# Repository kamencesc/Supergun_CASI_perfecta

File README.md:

# Supergun_CASI_perfecta
Diseño de un supergun con ciertas caracteristicas, proyecto en los foros de EOL.

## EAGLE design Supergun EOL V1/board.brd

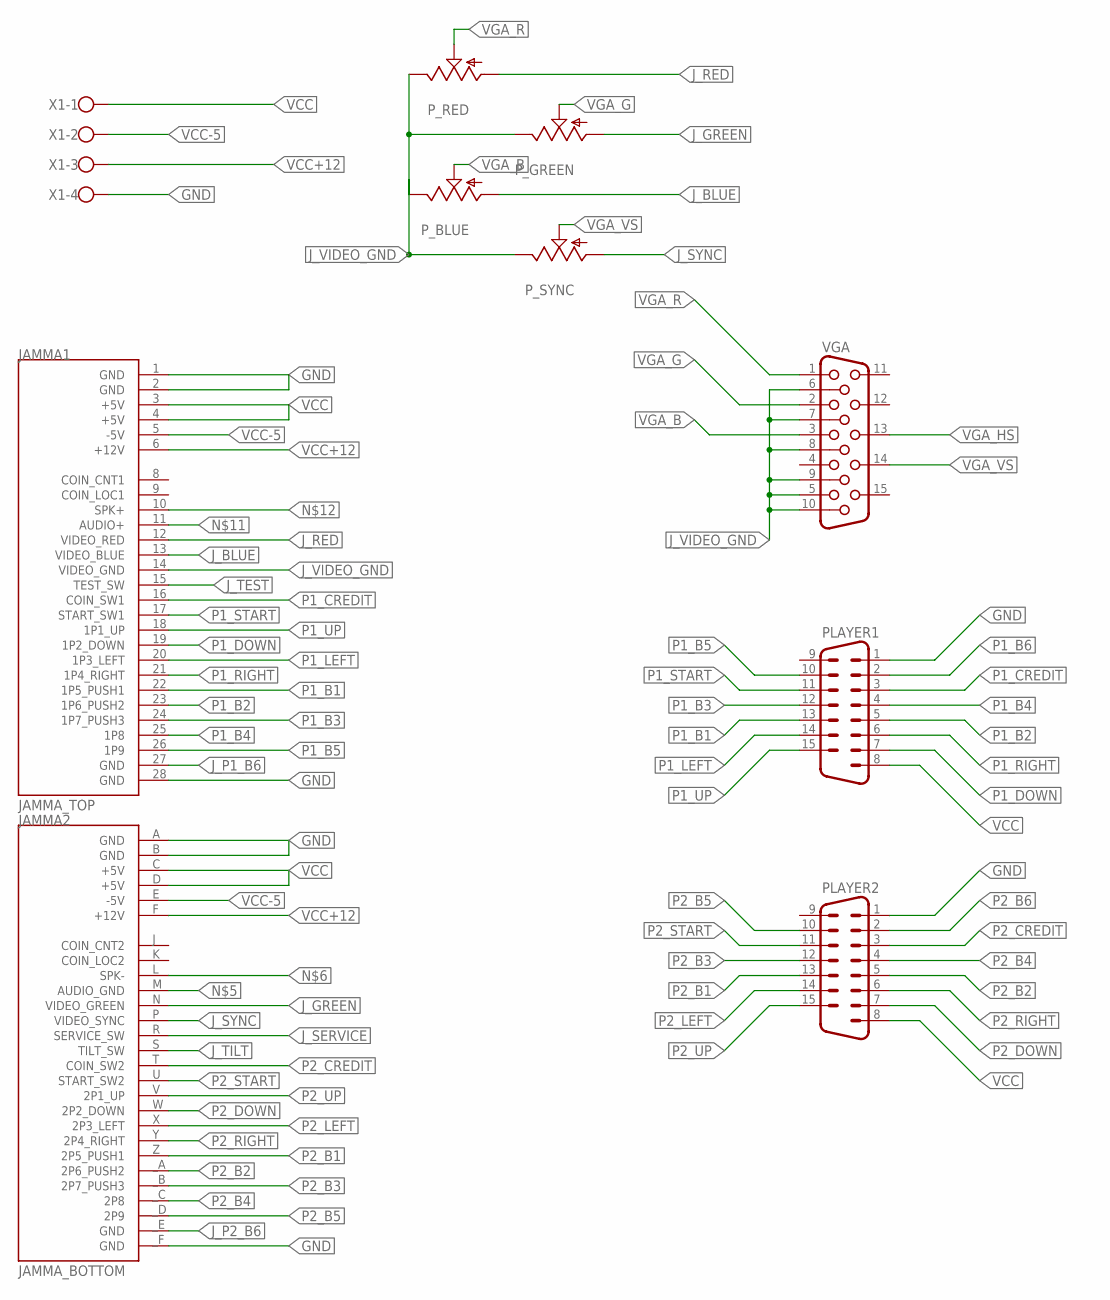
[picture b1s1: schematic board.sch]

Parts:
JAMMA1: JAMMA_TOP
JAMMA2: JAMMA_BOTTOM
PLAYER1, PLAYER2: M15VB
P_BLUE: TRIM_US-B25P; B25P
P_GREEN: TRIM_US-B25P; B25P
P_RED: TRIM_US-B25P; B25P
P_SYNC: TRIM_US-B25P; B25P
VGA: HF15H; HDF15H
X1: W237-4

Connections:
GND: JAMMA1.1 (GND), JAMMA1.2 (GND), JAMMA1.28 (GND), JAMMA2.A (GND), JAMMA2.B (GND), JAMMA2._F (GND), PLAYER1.1, PLAYER2.1, X1.4
J_BLUE: JAMMA1.13 (VIDEO_BLUE), P_BLUE.A
J_GREEN: JAMMA2.N (VIDEO_GREEN), P_GREEN.A
J_P1_B6: JAMMA1.27 (GND)
J_P2_B6: JAMMA2._E (GND)
J_RED: JAMMA1.12 (VIDEO_RED), P_RED.A
J_SERVICE: JAMMA2.R (SERVICE_SW)
J_SYNC: JAMMA2.P (VIDEO_SYNC), P_SYNC.A
J_TEST: JAMMA1.15 (TEST_SW)
J_TILT: JAMMA2.S (TILT_SW)
J_VIDEO_GND: JAMMA1.14 (VIDEO_GND), P_BLUE.E, P_GREEN.E, P_RED.E, P_SYNC.E, VGA.5, VGA.6, VGA.7, VGA.8, VGA.9, VGA.10
P1_B1: JAMMA1.22 (1P5_PUSH1), PLAYER1.13
P1_B2: JAMMA1.23 (1P6_PUSH2), PLAYER1.5
P1_B3: JAMMA1.24 (1P7_PUSH3), PLAYER1.12
P1_B4: JAMMA1.25 (1P8), PLAYER1.4
P1_B5: JAMMA1.26 (1P9), PLAYER1.10
P1_B6: PLAYER1.2
P1_CREDIT: JAMMA1.16 (COIN_SW1), PLAYER1.3
P1_DOWN: JAMMA1.19 (1P2_DOWN), PLAYER1.7
P1_LEFT: JAMMA1.20 (1P3_LEFT), PLAYER1.14
P1_RIGHT: JAMMA1.21 (1P4_RIGHT), PLAYER1.6
P1_START: JAMMA1.17 (START_SW1), PLAYER1.11
P1_UP: JAMMA1.18 (1P1_UP), PLAYER1.15
P2_B1: JAMMA2.Z (2P5_PUSH1), PLAYER2.13
P2_B2: JAMMA2._A (2P6_PUSH2), PLAYER2.5
P2_B3: JAMMA2._B (2P7_PUSH3), PLAYER2.12
P2_B4: JAMMA2._C (2P8), PLAYER2.4
P2_B5: JAMMA2._D (2P9), PLAYER2.10
P2_B6: PLAYER2.2
P2_CREDIT: JAMMA2.T (COIN_SW2), PLAYER2.3
P2_DOWN: JAMMA2.W (2P2_DOWN), PLAYER2.7
P2_LEFT: JAMMA2.X (2P3_LEFT), PLAYER2.14
P2_RIGHT: JAMMA2.Y (2P4_RIGHT), PLAYER2.6
P2_START: JAMMA2.U (START_SW2), PLAYER2.11
P2_UP: JAMMA2.V (2P1_UP), PLAYER2.15
VCC: JAMMA1.3 (+5V), JAMMA1.4 (+5V), JAMMA2.C (+5V), JAMMA2.D (+5V), PLAYER1.8, PLAYER2.8, X1.1
VCC+12: JAMMA1.6 (+12V), JAMMA2.F (+12V), X1.3
VCC-5: JAMMA1.5 (-5V), JAMMA2.E (-5V), X1.2
VGA_B: P_BLUE.S, VGA.3
VGA_G: P_GREEN.S, VGA.2
VGA_HS: VGA.13
VGA_R: P_RED.S, VGA.1
VGA_VS: P_SYNC.S, VGA.14

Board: 2 copper layers, 10 parts (2 on the bottom side), 35 nets, no tracks yet.

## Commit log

2018-05-01 Primera versión // First version
    Subida primera versión con cosa basicas, peine JAMMA (de https://github.com/Shinichi-Ohki/JAMMA_connector_for_eagle/blob/master/JAMMA.lbr), 2xDB15, VGA, conector de corriente.
    Upload te first versión, JAMMA connector (https://github.com/Shinichi-Ohki/JAMMA_connector_for_eagle/blob/master/JAMMA.lbr), 2xDB15, VGA, power connector.
